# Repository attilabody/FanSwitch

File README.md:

# FanSwitch

Simple MOSFET based circuit to switch additional fans with RAMPS servo outputs

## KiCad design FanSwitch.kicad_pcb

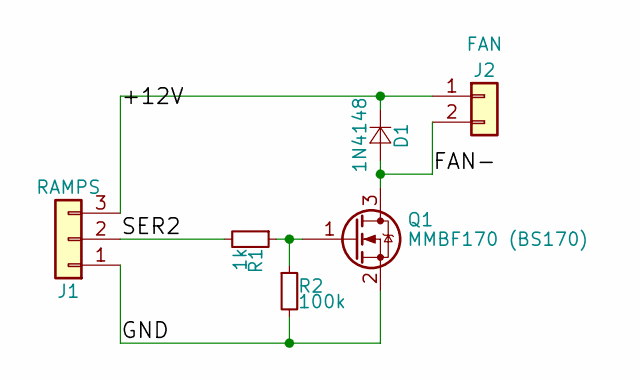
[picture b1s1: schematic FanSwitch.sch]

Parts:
D1: 1N4148; D_MiniMELF_Standard
J1: RAMPS; Pin_Header_Straight_1x03_Pitch2.54mm
J2: FAN; Pin_Header_Straight_1x02_Pitch2.54mm
Q1: MMBF170 (BS170); SOT-23_Handsoldering
R1: 1k; R_0805
R2: 100k; R_0805

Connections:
/+12V: D1.1 (K), J1.3, J2.1
/FAN-: D1.2 (A), J2.2, Q1.3 (D)
/GND: J1.1, Q1.2 (S), R2.2
/SER2: J1.2, R1.2
unnamed: Q1.1 (G), R1.1, R2.1

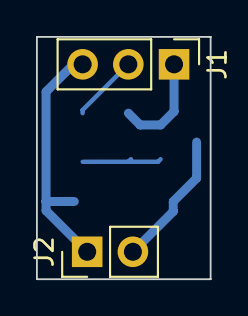
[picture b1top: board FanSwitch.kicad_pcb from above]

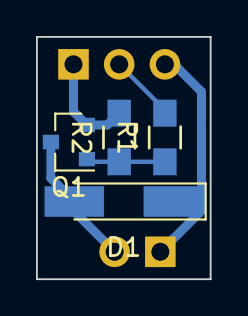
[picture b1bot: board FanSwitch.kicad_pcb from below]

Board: 2 copper layers, 9.7 x 13.5 mm, 6 parts (4 on the bottom side), 5 nets.
